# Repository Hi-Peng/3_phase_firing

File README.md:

# Pemicu Optik 3 Fasa

Ini merupakan repository untuk proyek pemicu 3 fasa.

Pengembangan meliput 
1. Pengembangan Firmware ARM Cortex M3 Prosesor pada STM32F401CC6U Mikrokontroller.
2. Pengembangan Hardware dari Sistem Pemicu Thyristor dan TRIAC.
3. Pengembangan User Interface untuk Pengendali Sudut Picu.

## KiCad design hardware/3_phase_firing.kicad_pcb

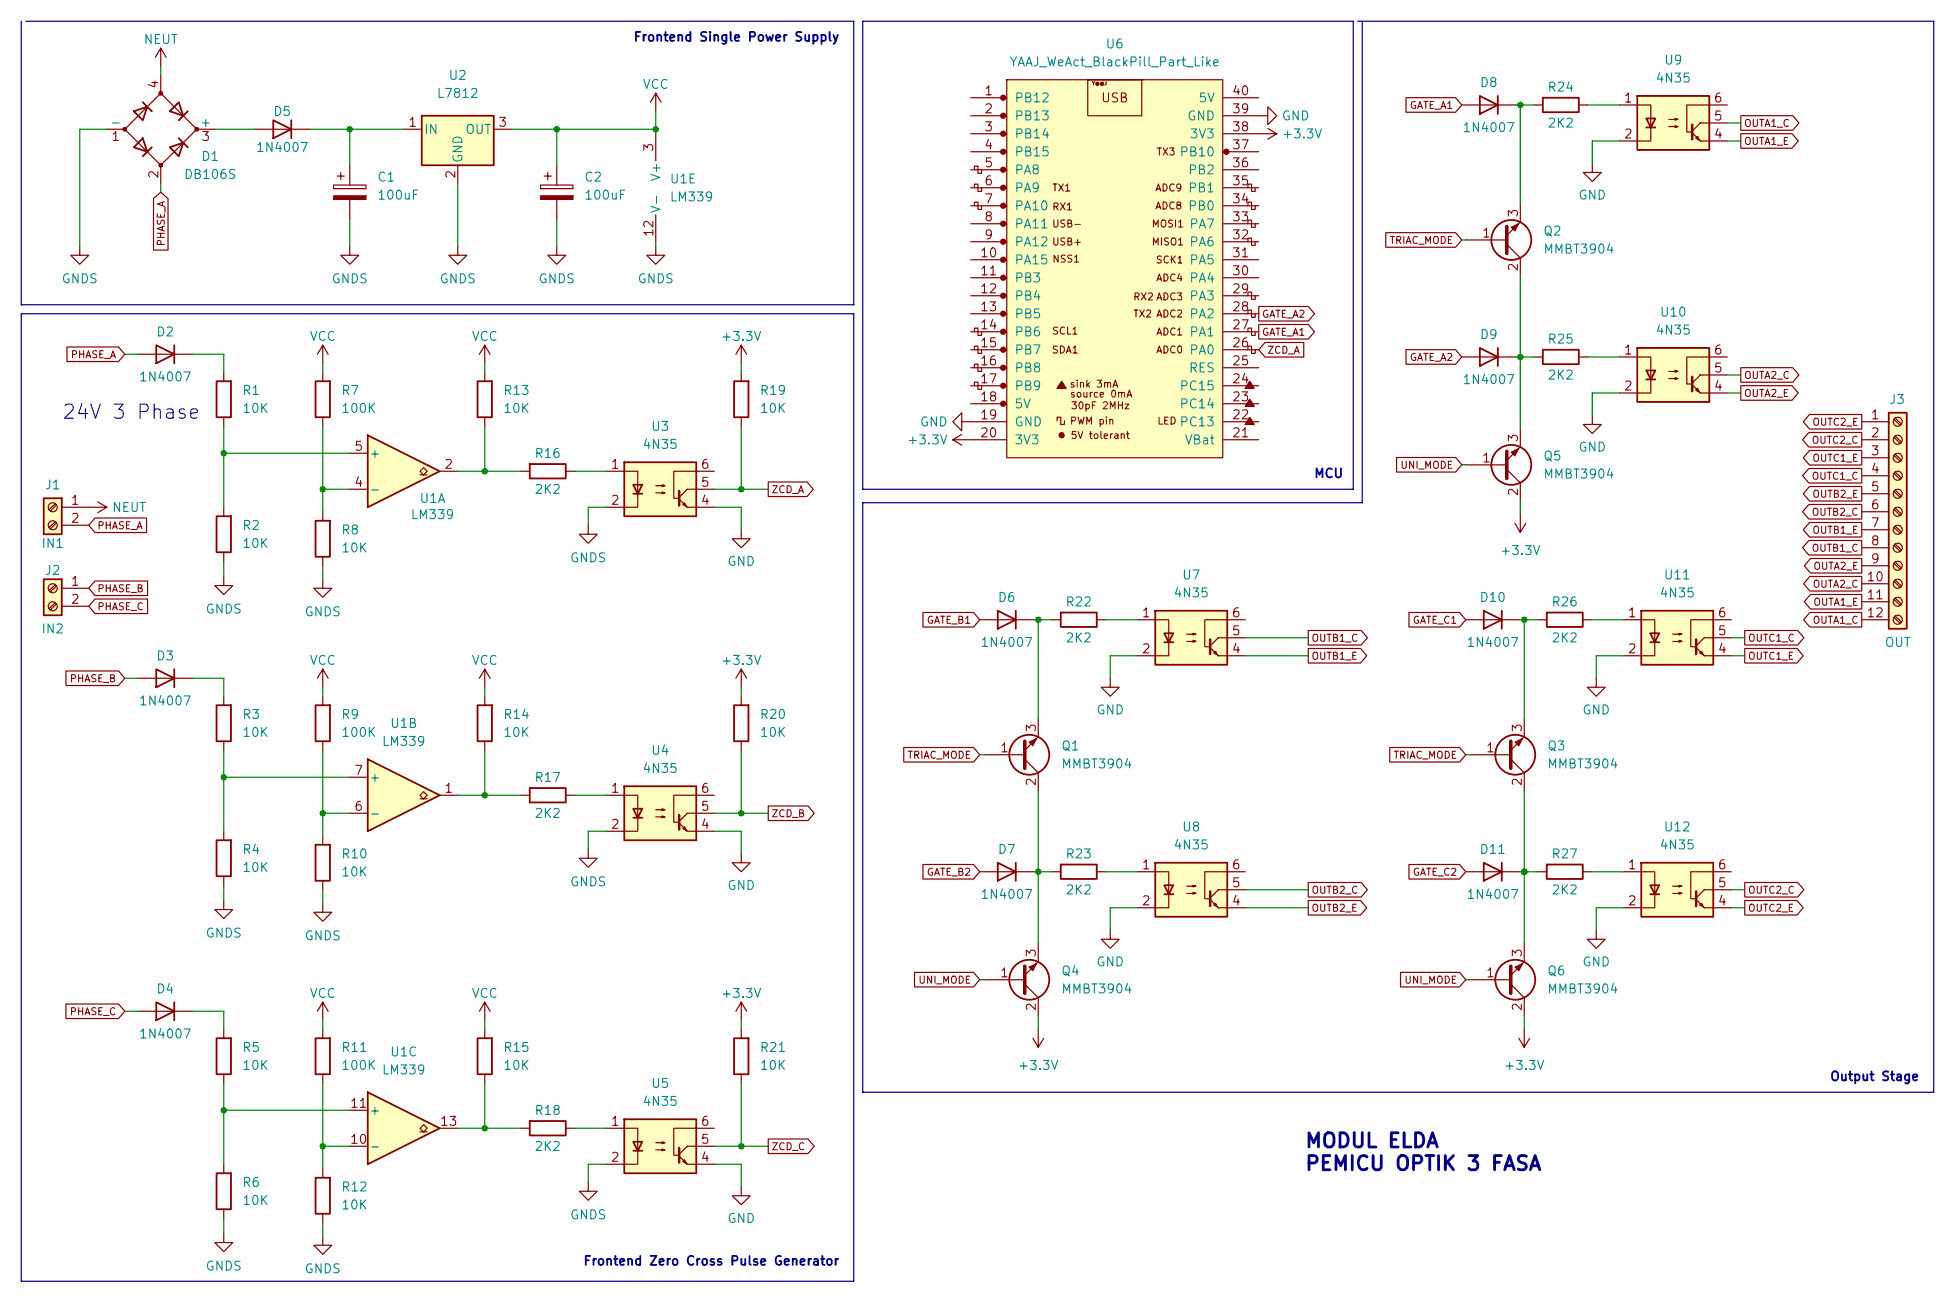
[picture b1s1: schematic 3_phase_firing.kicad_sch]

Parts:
C1, C2: 100uF; CP_Elec_6.3x7.7
D1: DB106S; Diode_Bridge_OnSemi_SDIP-4L
D2, D3, D4, D5, D6, D7, D8, D9, D10, D11: 1N4007; D_SMA_Handsoldering
J1: IN1; TerminalBlock_bornier-2_P5.08mm
J2: IN2; TerminalBlock_bornier-2_P5.08mm
J3: OUT; TerminalBlock_Phoenix_MKDS-3-12-5.08_1x12_P5.08mm_Horizontal
Q1, Q2, Q3, Q4, Q5, Q6: MMBT3904; SOT-23
R1, R2, R3, R4, R5, R6, R8, R10, R12, R13, R14, R15, R19, R20, R21: 10K; R_0805_2012Metric
R7, R9, R11: 100K; R_0805_2012Metric
R16, R17, R18, R22, R23, R24, R25, R26, R27: 2K2; R_0805_2012Metric
U1: LM339; SOIC-14_3.9x8.7mm_P1.27mm
U2: L7812; TO-263-2
U3, U4, U5, U7, U8, U9, U10, U11, U12: 4N35; DIP-6_W8.89mm_SMDSocket_LongPads
U6: YAAJ_WeAct_BlackPill_Part_Like; YAAJ_WeAct_BlackPill_2

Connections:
+3.3V: Q4.2 (C), Q5.2 (C), Q6.2 (C), R19.2, R20.2, R21.2, U6.20 (3V3), U6.38 (3V3)
GATE_A1: D8.2 (A), U6.27 (PA1)
GATE_A2: D9.2 (A), U6.28 (PA2)
GATE_B1: D6.2 (A)
GATE_B2: D7.2 (A)
GATE_C1: D10.2 (A)
GATE_C2: D11.2 (A)
GND: U3.4, U4.4, U5.4, U6.19 (GND), U6.39 (GND), U7.2, U8.2, U9.2, U10.2, U11.2, U12.2
GNDS: C1.2, C2.2, D1.1 (-), R2.1, R4.1, R6.1, R8.1, R10.1, R12.1, U1.12 (V-), U2.2 (GND), U3.2, U4.2, U5.2
NEUT: D1.4, J1.1
unnamed: C1.1, D5.1 (K), U2.1 (IN)
unnamed: D1.3 (+), D5.2 (A)
unnamed: D2.1 (K), R1.2
unnamed: D3.1 (K), R3.2
unnamed: D4.1 (K), R5.2
unnamed: D6.1 (K), Q1.3 (E), R22.2
unnamed: D7.1 (K), Q1.2 (C), Q4.3 (E), R23.2
unnamed: D8.1 (K), Q2.3 (E), R24.2
unnamed: D9.1 (K), Q2.2 (C), Q5.3 (E), R25.2
unnamed: D10.1 (K), Q3.3 (E), R26.2
unnamed: D11.1 (K), Q3.2 (C), Q6.3 (E), R27.2
unnamed: R1.1, R2.2, U1.5 (+)
unnamed: R3.1, R4.2, U1.7 (+)
unnamed: R5.1, R6.2, U1.11 (+)
unnamed: R7.1, R8.2, U1.4 (-)
unnamed: R9.1, R10.2, U1.6 (-)
unnamed: R11.1, R12.2, U1.10 (-)
unnamed: R13.1, R16.2, U1.2
unnamed: R14.1, R17.2, U1.1
unnamed: R15.1, R18.2, U1.13
unnamed: R16.1, U3.1
unnamed: R17.1, U4.1
unnamed: R18.1, U5.1
unnamed: R22.1, U7.1
unnamed: R23.1, U8.1
unnamed: R24.1, U9.1
unnamed: R25.1, U10.1
unnamed: R26.1, U11.1
unnamed: R27.1, U12.1
OUTA1_C: J3.12, U9.5
OUTA1_E: J3.11, U9.4
OUTA2_C: J3.10, U10.5
OUTA2_E: J3.9, U10.4
OUTB1_C: J3.8, U7.5
OUTB1_E: J3.7, U7.4
OUTB2_C: J3.6, U8.5
OUTB2_E: J3.5, U8.4
OUTC1_C: J3.4, U11.5
OUTC1_E: J3.3, U11.4
OUTC2_C: J3.2, U12.5
OUTC2_E: J3.1, U12.4
PHASE_A: D1.2, D2.2 (A), J1.2
PHASE_B: D3.2 (A), J2.1
PHASE_C: D4.2 (A), J2.2
TRIAC_MODE: Q1.1 (B), Q2.1 (B), Q3.1 (B)
UNI_MODE: Q4.1 (B), Q5.1 (B), Q6.1 (B)
VCC: C2.1, R7.2, R9.2, R11.2, R13.2, R14.2, R15.2, U1.3 (V+), U2.3 (OUT)
ZCD_A: R19.1, U3.5, U6.26 (PA0)
ZCD_B: R20.1, U4.5
ZCD_C: R21.1, U5.5

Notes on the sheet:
MODUL ELDA PEMICU OPTIK 3 FASA
Frontend Zero Cross Pulse Generator
MCU
Frontend Single Power Supply
24V 3 Phase
Output Stage

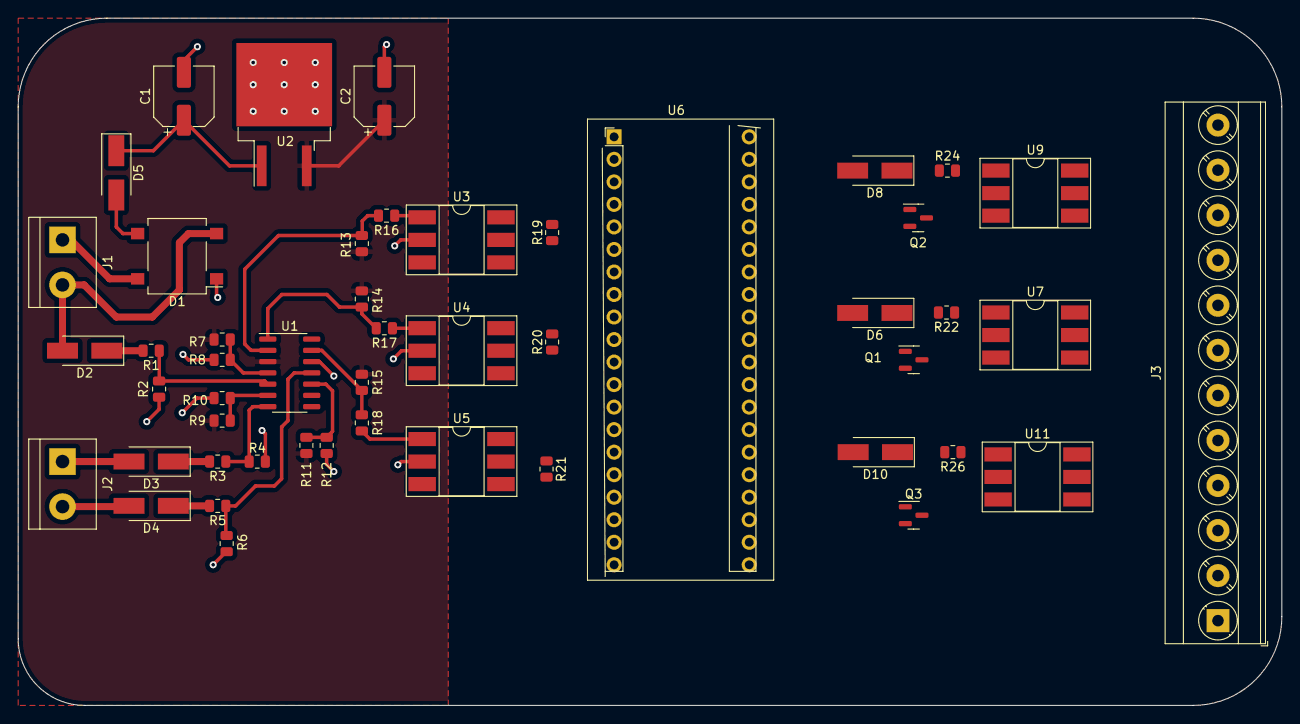
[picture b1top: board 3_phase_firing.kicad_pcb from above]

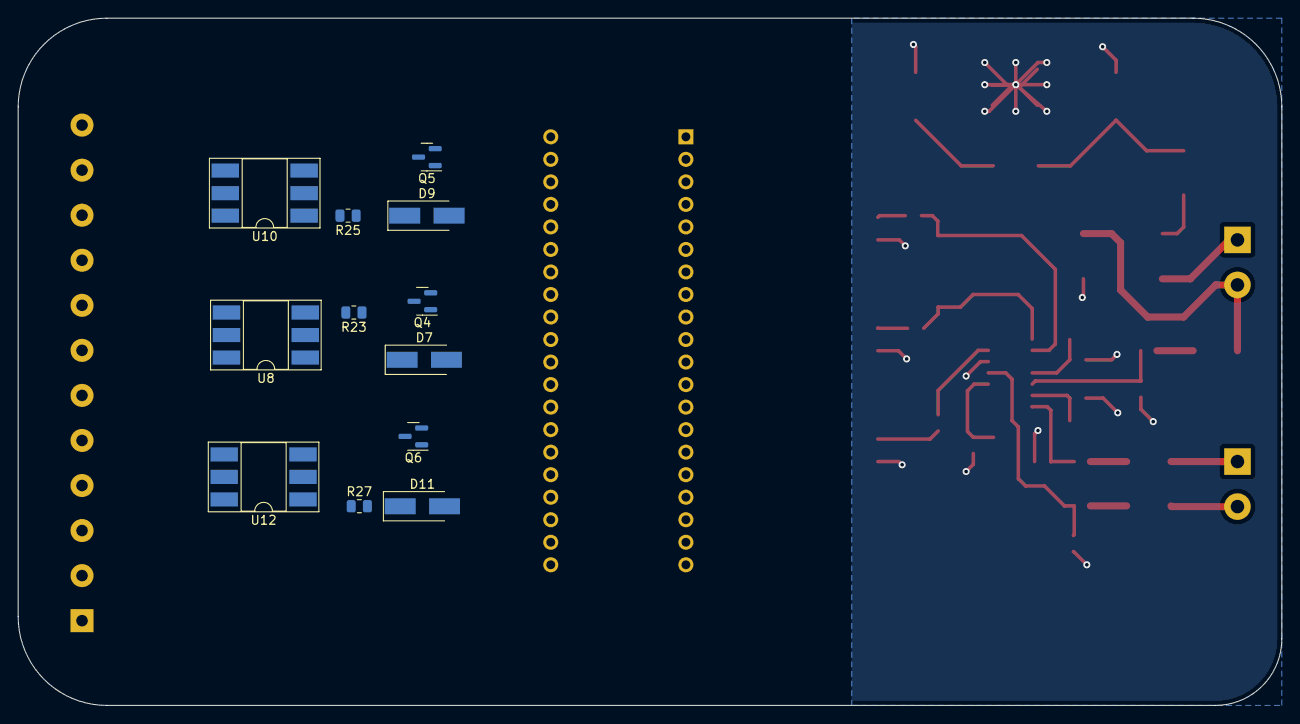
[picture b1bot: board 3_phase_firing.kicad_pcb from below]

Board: 2 copper layers, 142.5 x 77.5 mm, 61 parts (12 on the bottom side), 56 nets.

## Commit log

2022-07-10 repo init
2022-07-10 completing zero detector circuit
2022-07-10 adding readme
2022-07-11 done with schematic + pcb
2022-07-11 pcb done
2022-07-12 updating gitignore
2022-07-12 reconfiguring timers and clocks
2022-07-19 one pulse mode trial 1
2022-07-20 adding one pulse already working starting to do the unidirectional
2022-07-23 Updating the HAL Libs
2022-07-27 trying OC toggle, refer RM page 386
2022-07-28 hw dev commit
2022-07-28 creating stm32f4 project and fixing ZDC Circuit and changing to blackpill STM32F4
2022-07-31 adding ui
2022-08-03 done with one phase
2022-08-03 remaking schematic and done with footprint assignment
2022-08-03 modifying footprint
2022-08-04 done with pcb layouting, routing need to done more
2022-08-04 hardware done, not reviewed yet
2022-08-13 nambahin Readme dikit
2022-08-18 Create CAD model
    Creating CAD model
2022-08-18 finishing cad and renderings
2022-08-21 tracing path of the pcb
2022-08-21 Revert "tracing path of the pcb"
    This reverts commit a1f78cd755137d86b9aab8dfdd90e54233a75f74.
2022-08-21 fixing kicad_pcb files
2022-10-10 changing dimension of the enclosure
2022-11-07 changing this repository to only firmware development
2023-02-15 adding more aux mode, timer, and encoder setup
2023-02-15 adding more aux, encoder, and configure timer
